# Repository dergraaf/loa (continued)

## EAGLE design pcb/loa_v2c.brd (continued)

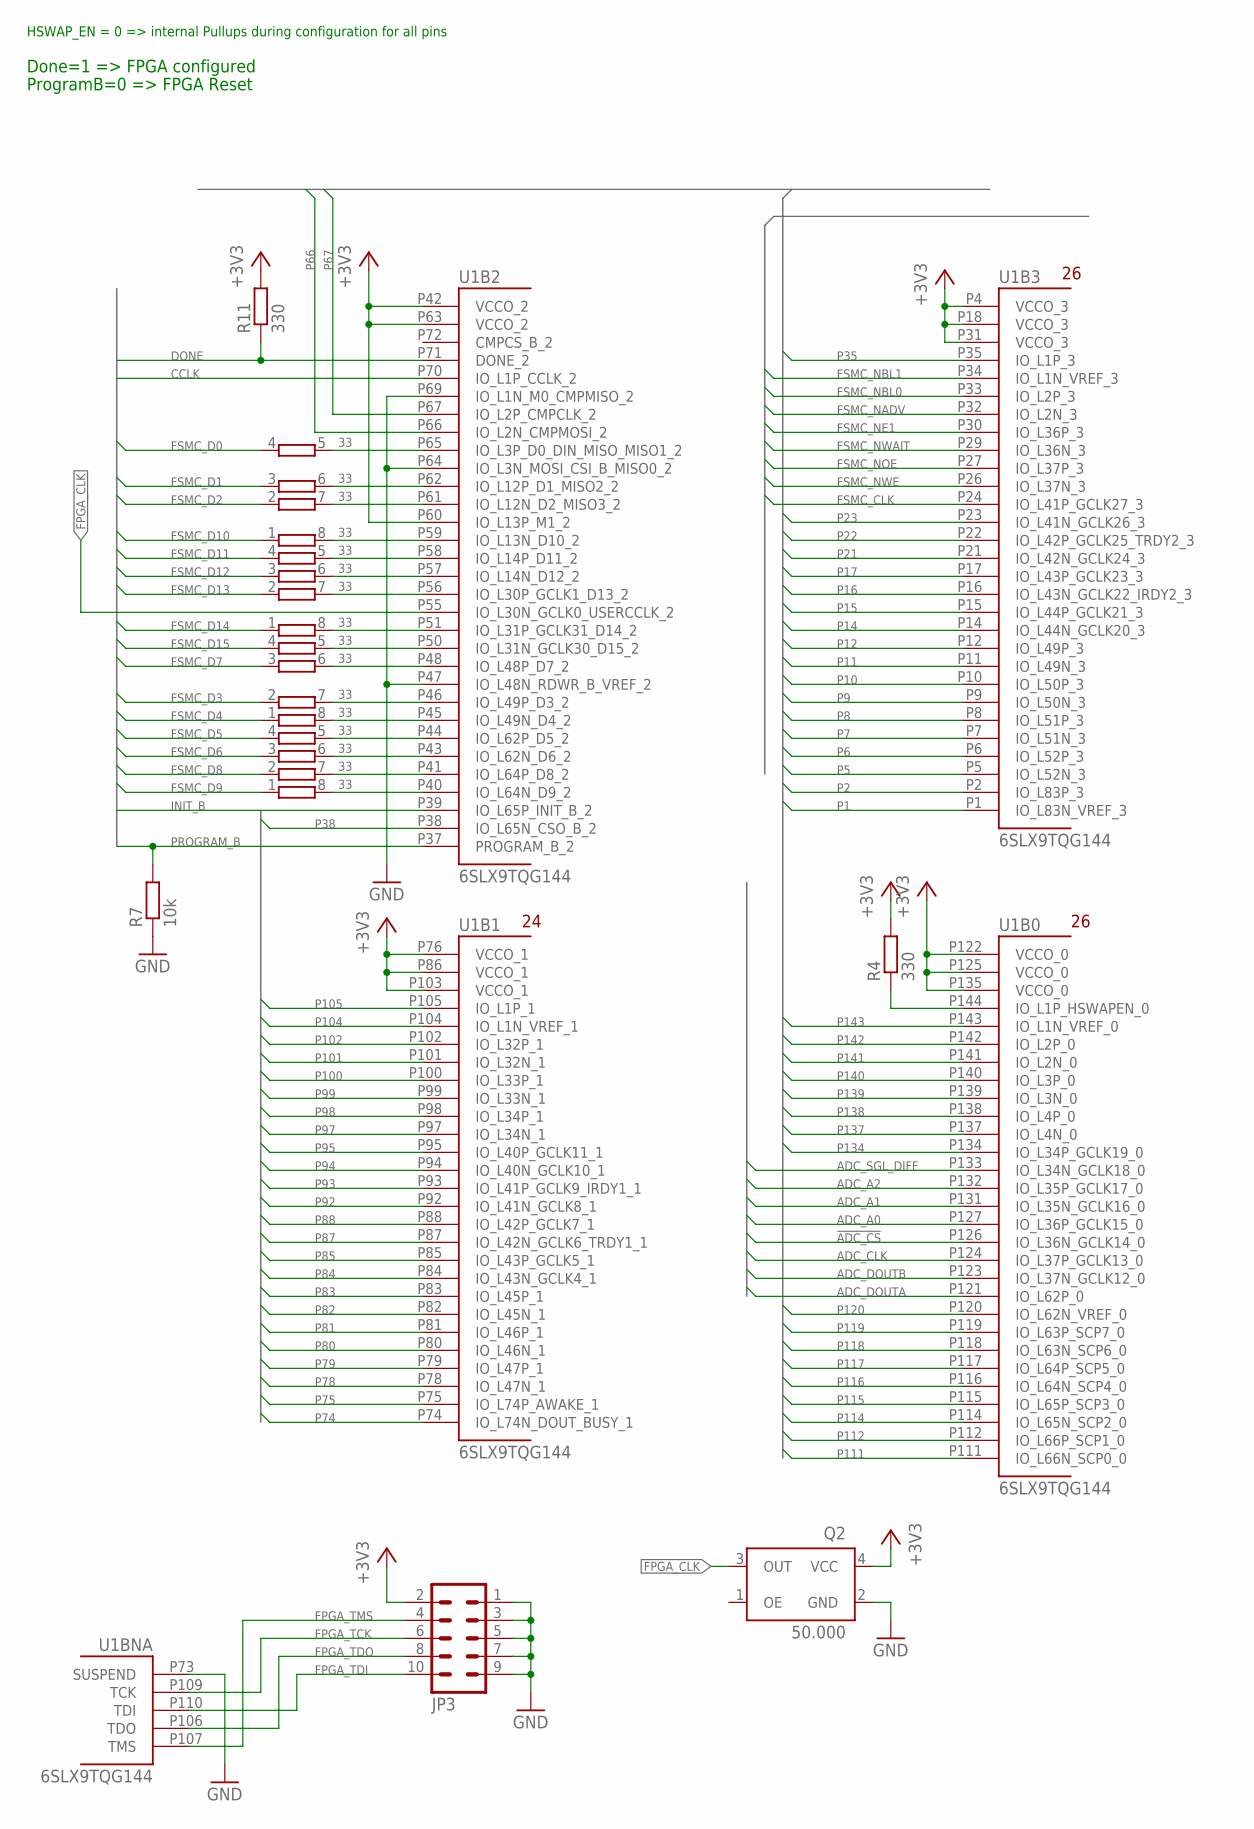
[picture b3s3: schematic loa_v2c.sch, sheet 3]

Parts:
JP3: ML10S
Q2: 50.000; XO53
R4, R11: 330; R0603
R7: 10k; R0603
RN3, RN4, RN6, RN7: 33; EXB38V
U1: 6SLX9TQG144; TQ144

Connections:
!ADC_CS: U1.P126 (IO_L36N_GCLK14_0); also elsewhere on the board
+3V3: JP3.2, Q2.4 (VCC), R4.2, R11.2, U1.P4 (VCCO_3), U1.P18 (VCCO_3), U1.P31 (VCCO_3), U1.P42 (VCCO_2), U1.P60 (IO_L13P_M1_2), U1.P63 (VCCO_2), U1.P76 (VCCO_1), U1.P86 (VCCO_1), U1.P103 (VCCO_1), U1.P122 (VCCO_0), U1.P125 (VCCO_0), U1.P135 (VCCO_0); also elsewhere on the board
ADC_A0: U1.P127 (IO_L36P_GCLK15_0); also elsewhere on the board
ADC_A1: U1.P131 (IO_L35N_GCLK16_0); also elsewhere on the board
ADC_A2: U1.P132 (IO_L35P_GCLK17_0); also elsewhere on the board
ADC_CLK: U1.P124 (IO_L37P_GCLK13_0); also elsewhere on the board
ADC_DOUTA: U1.P121 (IO_L62P_0); also elsewhere on the board
ADC_DOUTB: U1.P123 (IO_L37N_GCLK12_0); also elsewhere on the board
ADC_SGL_DIFF: U1.P133 (IO_L34N_GCLK18_0); also elsewhere on the board
CCLK: U1.P70 (IO_L1P_CCLK_2); also elsewhere on the board
DONE: R11.1, U1.P71 (DONE_2); also elsewhere on the board
FPGA_CLK: Q2.3 (OUT), U1.P55 (IO_L30N_GCLK0_USERCCLK_2)
FPGA_TCK: JP3.6, U1.P109 (TCK)
FPGA_TDI: JP3.10, U1.P110 (TDI)
FPGA_TDO: JP3.8, U1.P106 (TDO)
FPGA_TMS: JP3.4, U1.P107 (TMS)
FSMC_CLK: U1.P24 (IO_L41P_GCLK27_3); also elsewhere on the board
FSMC_D0: RN3.4 (1); also elsewhere on the board
FSMC_D1: RN3.3 (1); also elsewhere on the board
FSMC_D2: RN3.2 (1); also elsewhere on the board
FSMC_D3: RN7.2 (1); also elsewhere on the board
FSMC_D4: RN7.1; also elsewhere on the board
FSMC_D5: RN4.4 (1); also elsewhere on the board
FSMC_D6: RN4.3 (1); also elsewhere on the board
FSMC_D7: RN7.3 (1); also elsewhere on the board
FSMC_D8: RN4.2 (1); also elsewhere on the board
FSMC_D9: RN4.1; also elsewhere on the board
FSMC_D10: RN3.1; also elsewhere on the board
FSMC_D11: RN6.4 (1); also elsewhere on the board
FSMC_D12: RN6.3 (1); also elsewhere on the board
FSMC_D13: RN6.2 (1); also elsewhere on the board
FSMC_D14: RN6.1; also elsewhere on the board
FSMC_D15: RN7.4 (1); also elsewhere on the board
FSMC_NADV: U1.P32 (IO_L2N_3); also elsewhere on the board
FSMC_NBL0: U1.P33 (IO_L2P_3); also elsewhere on the board
FSMC_NBL1: U1.P34 (IO_L1N_VREF_3); also elsewhere on the board
FSMC_NE1: U1.P30 (IO_L36P_3); also elsewhere on the board
FSMC_NOE: U1.P27 (IO_L37P_3); also elsewhere on the board
FSMC_NWAIT: U1.P29 (IO_L36N_3); also elsewhere on the board
FSMC_NWE: U1.P26 (IO_L37N_3); also elsewhere on the board
GND: JP3.1, JP3.3, JP3.5, JP3.7, JP3.9, Q2.2 (GND), R7.1, U1.P47 (IO_L48N_RDWR_B_VREF_2), U1.P64 (IO_L3N_MOSI_CSI_B_MISO0_2), U1.P69 (IO_L1N_M0_CMPMISO_2), U1.P73 (SUSPEND); also elsewhere on the board
INIT_B: U1.P39 (IO_L65P_INIT_B_2); also elsewhere on the board
unnamed: RN3.5 (2), U1.P65 (IO_L3P_D0_DIN_MISO_MISO1_2)
unnamed: RN3.6 (2), U1.P62 (IO_L12P_D1_MISO2_2)
unnamed: RN3.7 (2), U1.P61 (IO_L12N_D2_MISO3_2)
unnamed: RN3.8 (2), U1.P59 (IO_L13N_D10_2)
unnamed: RN6.5 (2), U1.P58 (IO_L14P_D11_2)
unnamed: RN6.6 (2), U1.P57 (IO_L14N_D12_2)
unnamed: RN6.7 (2), U1.P56 (IO_L30P_GCLK1_D13_2)
unnamed: RN6.8 (2), U1.P51 (IO_L31P_GCLK31_D14_2)
unnamed: RN7.5 (2), U1.P50 (IO_L31N_GCLK30_D15_2)
unnamed: RN7.6 (2), U1.P48 (IO_L48P_D7_2)
unnamed: RN7.7 (2), U1.P46 (IO_L49P_D3_2)
unnamed: RN7.8 (2), U1.P45 (IO_L49N_D4_2)
unnamed: RN4.5 (2), U1.P44 (IO_L62P_D5_2)
unnamed: R4.1, U1.P144 (IO_L1P_HSWAPEN_0)
unnamed: RN4.7 (2), U1.P41 (IO_L64P_D8_2)
unnamed: RN4.6 (2), U1.P43 (IO_L62N_D6_2)
unnamed: RN4.8 (2), U1.P40 (IO_L64N_D9_2)
P1: U1.P1 (IO_L83N_VREF_3); also elsewhere on the board
P2: U1.P2 (IO_L83P_3); also elsewhere on the board
P5: U1.P5 (IO_L52N_3); also elsewhere on the board
P6: U1.P6 (IO_L52P_3); also elsewhere on the board
P7: U1.P7 (IO_L51N_3); also elsewhere on the board
P8: U1.P8 (IO_L51P_3); also elsewhere on the board
P9: U1.P9 (IO_L50N_3); also elsewhere on the board
P10: U1.P10 (IO_L50P_3); also elsewhere on the board
P11: U1.P11 (IO_L49N_3); also elsewhere on the board
P12: U1.P12 (IO_L49P_3); also elsewhere on the board
P14: U1.P14 (IO_L44N_GCLK20_3); also elsewhere on the board
P15: U1.P15 (IO_L44P_GCLK21_3); also elsewhere on the board
P16: U1.P16 (IO_L43N_GCLK22_IRDY2_3); also elsewhere on the board
P17: U1.P17 (IO_L43P_GCLK23_3); also elsewhere on the board
P21: U1.P21 (IO_L42N_GCLK24_3); also elsewhere on the board
P22: U1.P22 (IO_L42P_GCLK25_TRDY2_3); also elsewhere on the board
P23: U1.P23 (IO_L41N_GCLK26_3); also elsewhere on the board
P35: U1.P35 (IO_L1P_3); also elsewhere on the board
P38: U1.P38 (IO_L65N_CSO_B_2); also elsewhere on the board
P66: U1.P66 (IO_L2N_CMPMOSI_2); also elsewhere on the board
P67: U1.P67 (IO_L2P_CMPCLK_2); also elsewhere on the board
P74: U1.P74 (IO_L74N_DOUT_BUSY_1); also elsewhere on the board
P75: U1.P75 (IO_L74P_AWAKE_1); also elsewhere on the board
P78: U1.P78 (IO_L47N_1); also elsewhere on the board
P79: U1.P79 (IO_L47P_1); also elsewhere on the board
P80: U1.P80 (IO_L46N_1); also elsewhere on the board
P81: U1.P81 (IO_L46P_1); also elsewhere on the board
P82: U1.P82 (IO_L45N_1); also elsewhere on the board
P83: U1.P83 (IO_L45P_1); also elsewhere on the board
P84: U1.P84 (IO_L43N_GCLK4_1); also elsewhere on the board
P85: U1.P85 (IO_L43P_GCLK5_1); also elsewhere on the board
P87: U1.P87 (IO_L42N_GCLK6_TRDY1_1); also elsewhere on the board
P88: U1.P88 (IO_L42P_GCLK7_1); also elsewhere on the board
P92: U1.P92 (IO_L41N_GCLK8_1); also elsewhere on the board
P93: U1.P93 (IO_L41P_GCLK9_IRDY1_1); also elsewhere on the board
P94: U1.P94 (IO_L40N_GCLK10_1); also elsewhere on the board
P95: U1.P95 (IO_L40P_GCLK11_1); also elsewhere on the board
P97: U1.P97 (IO_L34N_1); also elsewhere on the board
P98: U1.P98 (IO_L34P_1); also elsewhere on the board
P99: U1.P99 (IO_L33N_1); also elsewhere on the board
P100: U1.P100 (IO_L33P_1); also elsewhere on the board
P101: U1.P101 (IO_L32N_1); also elsewhere on the board
P102: U1.P102 (IO_L32P_1); also elsewhere on the board
P104: U1.P104 (IO_L1N_VREF_1); also elsewhere on the board
P105: U1.P105 (IO_L1P_1); also elsewhere on the board
P111: U1.P111 (IO_L66N_SCP0_0); also elsewhere on the board
P112: U1.P112 (IO_L66P_SCP1_0); also elsewhere on the board
P114: U1.P114 (IO_L65N_SCP2_0); also elsewhere on the board
P115: U1.P115 (IO_L65P_SCP3_0); also elsewhere on the board
P116: U1.P116 (IO_L64N_SCP4_0); also elsewhere on the board
P117: U1.P117 (IO_L64P_SCP5_0); also elsewhere on the board
P118: U1.P118 (IO_L63N_SCP6_0); also elsewhere on the board
P119: U1.P119 (IO_L63P_SCP7_0); also elsewhere on the board
P120: U1.P120 (IO_L62N_VREF_0); also elsewhere on the board
P134: U1.P134 (IO_L34P_GCLK19_0); also elsewhere on the board
P137: U1.P137 (IO_L4N_0); also elsewhere on the board
P138: U1.P138 (IO_L4P_0); also elsewhere on the board
P139: U1.P139 (IO_L3N_0); also elsewhere on the board
P140: U1.P140 (IO_L3P_0); also elsewhere on the board
P141: U1.P141 (IO_L2N_0); also elsewhere on the board
P142: U1.P142 (IO_L2P_0); also elsewhere on the board
P143: U1.P143 (IO_L1N_VREF_0); also elsewhere on the board
PROGRAM_B: R7.2, U1.P37 (PROGRAM_B_2); also elsewhere on the board

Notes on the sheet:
Done=1 => FPGA configured
ProgramB=0 => FPGA Reset
HSWAP_EN = 0 => internal Pullups during configuration for all pins

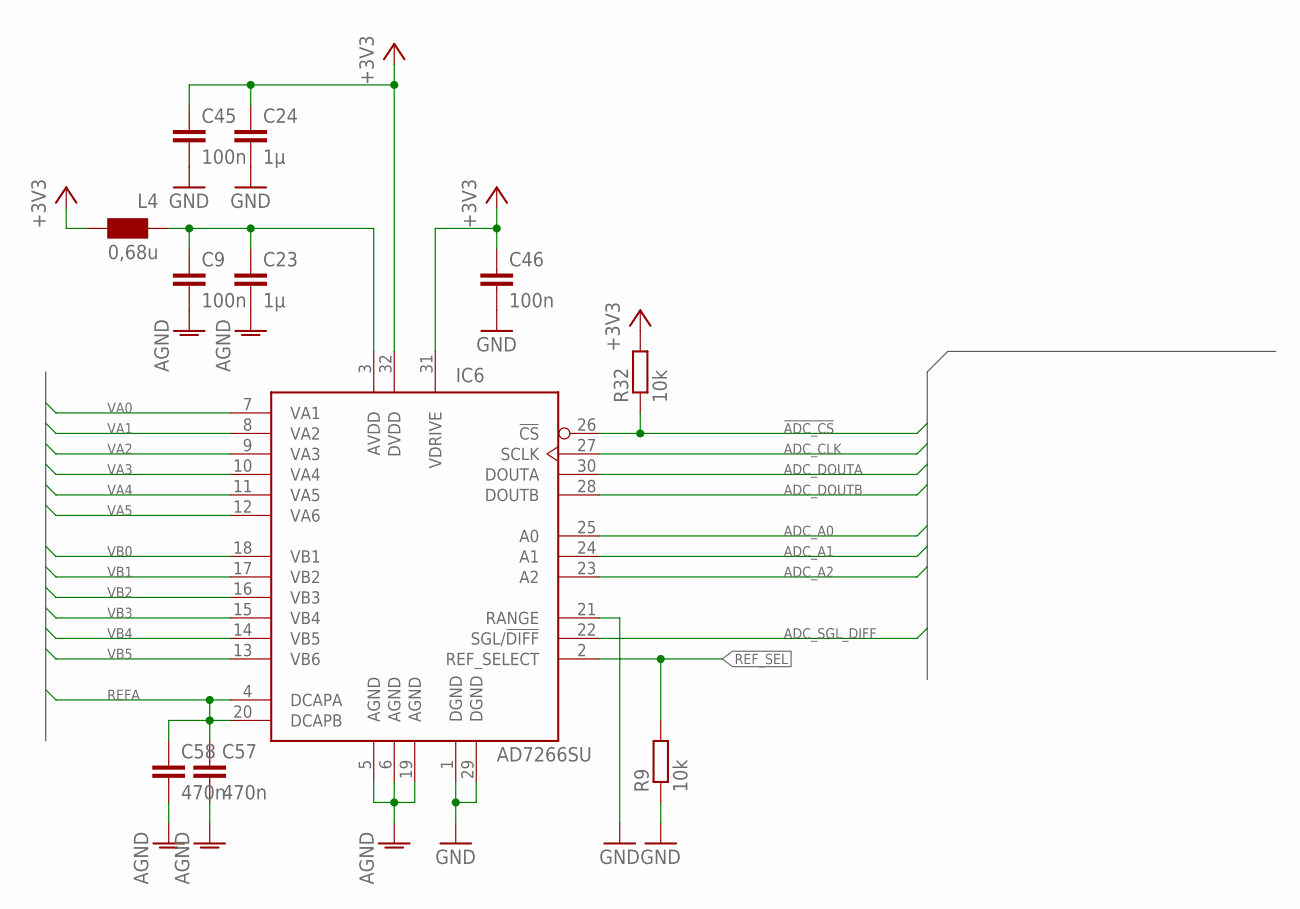
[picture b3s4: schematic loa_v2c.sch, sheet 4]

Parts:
C9, C45, C46: 100n; C0603
C23, C24: 1µ; C0805
C57, C58: 470n; C0805
IC6: AD7266SU; TQFP32-08
L4: 0,68u; WE-KI_0805_B
R9, R32: 10k; R0603

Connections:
!ADC_CS: IC6.26 (!CS), R32.1; also elsewhere on the board
+3V3: C24.1, C45.1, C46.1, IC6.31 (VDRIVE), IC6.32 (DVDD), L4.1 (2), R32.2; also elsewhere on the board
ADC_A0: IC6.25 (A0); also elsewhere on the board
ADC_A1: IC6.24 (A1); also elsewhere on the board
ADC_A2: IC6.23 (A2); also elsewhere on the board
ADC_CLK: IC6.27 (SCLK); also elsewhere on the board
ADC_DOUTA: IC6.30 (DOUTA); also elsewhere on the board
ADC_DOUTB: IC6.28 (DOUTB); also elsewhere on the board
ADC_SGL_DIFF: IC6.22 (SGL/!DIFF); also elsewhere on the board
AGND: C9.2, C23.2, C57.2, C58.2, IC6.5 (AGND), IC6.6 (AGND), IC6.19 (AGND); also elsewhere on the board
GND: C24.2, C45.2, C46.2, IC6.1 (DGND), IC6.21 (RANGE), IC6.29 (DGND), R9.1; also elsewhere on the board
unnamed: C9.1, C23.1, IC6.3 (AVDD), L4.2 (1)
REFA: C57.1, C58.1, IC6.4 (DCAPA), IC6.20 (DCAPB); also elsewhere on the board
REF_SEL: IC6.2 (REF_SELECT), R9.2; also elsewhere on the board
VA0: IC6.7 (VA1); also elsewhere on the board
VA1: IC6.8 (VA2); also elsewhere on the board
VA2: IC6.9 (VA3); also elsewhere on the board
VA3: IC6.10 (VA4); also elsewhere on the board
VA4: IC6.11 (VA5); also elsewhere on the board
VA5: IC6.12 (VA6); also elsewhere on the board
VB0: IC6.18 (VB1); also elsewhere on the board
VB1: IC6.17 (VB2); also elsewhere on the board
VB2: IC6.16 (VB3); also elsewhere on the board
VB3: IC6.15 (VB4); also elsewhere on the board
VB4: IC6.14 (VB5); also elsewhere on the board
VB5: IC6.13 (VB6); also elsewhere on the board

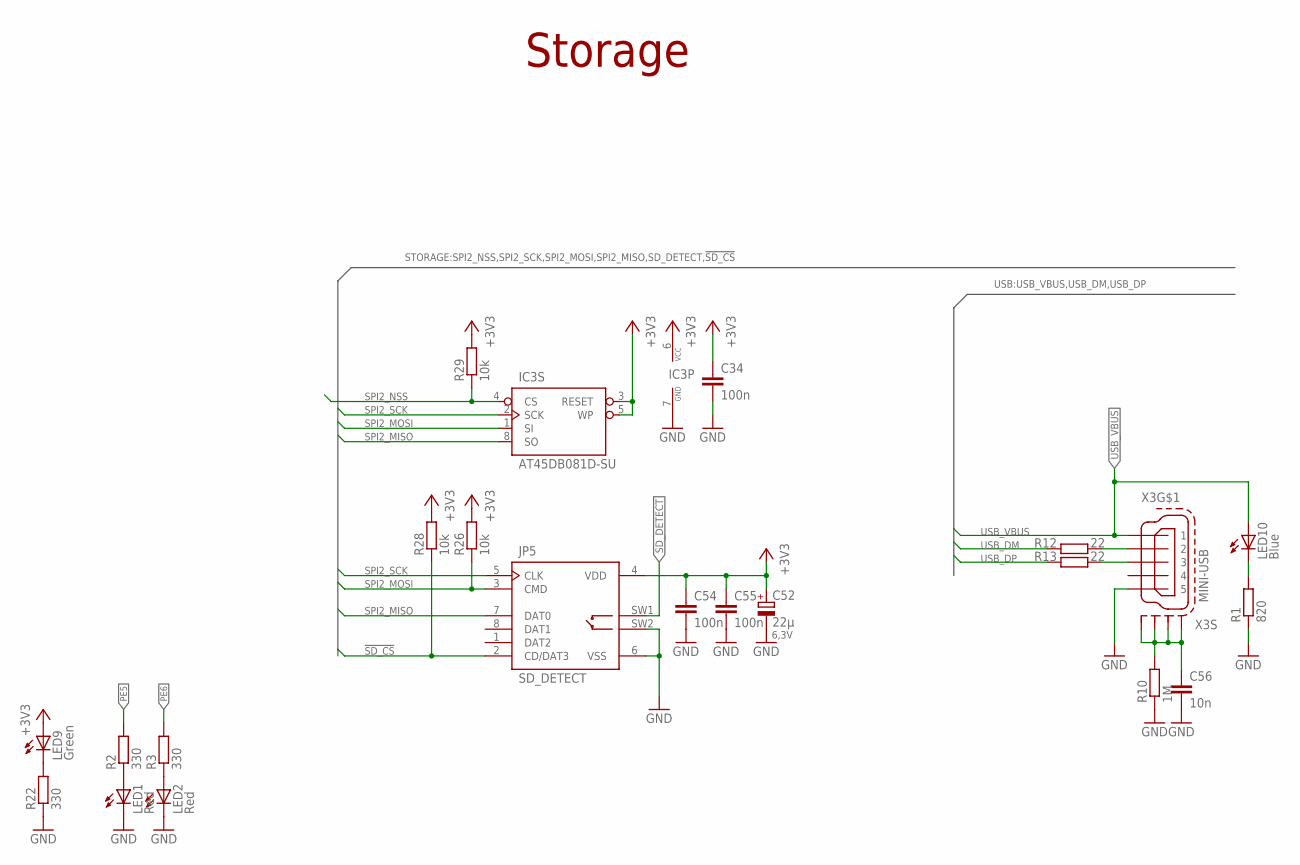
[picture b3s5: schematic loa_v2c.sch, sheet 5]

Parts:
C34, C54, C55: 100n; C0603
C52: 22µ; SMC_C; VOLTAGE 6,3V
C56: 10n; C0603
IC3: AT45DB081D-SU; SO08
JP5: SD_DETECT; SD_MOLEX_49225-0821
LED1, LED2: Red; CHIPLED_0805
LED9: Green; CHIPLED_0805
LED10: Blue; CHIPLED_0805
R1: 820; R0805
R2, R3, R22: 330; R0603
R10: 1M; R0805
R12, R13: 22; R0603
R26, R28, R29: 10k; R0603
X3: MINI-USB; 32005-201

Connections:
!SD_CS: JP5.2 (CD/DAT3), R28.1; also elsewhere on the board
+3V3: C34.1, C52.+, C54.1, C55.1, IC3.3 (RESET), IC3.5 (WP), IC3.6 (VCC), JP5.4 (VDD), LED9.A, R26.2, R28.2, R29.2; also elsewhere on the board
GND: C34.2, C52.-, C54.2, C55.2, C56.2, IC3.7 (GND), JP5.6 (VSS), JP5.SW2, LED1.C, LED2.C, R1.1, R10.1, R22.1, X3.5; also elsewhere on the board
unnamed: LED1.A, R2.1
unnamed: R12.2, X3.2
unnamed: R13.2, X3.3
unnamed: LED2.A, R3.1
unnamed: LED9.C, R22.2
unnamed: LED10.C, R1.2
unnamed: C56.1, R10.2, X3.M1 (S1), X3.M2 (S2), X3.M3 (S3), X3.M4 (S4)
PE5: R2.2; also elsewhere on the board
PE6: R3.2; also elsewhere on the board
SD_DETECT: JP5.SW1; also elsewhere on the board
SPI2_MISO: IC3.8 (SO), JP5.7 (DAT0); also elsewhere on the board
SPI2_MOSI: IC3.1 (SI), JP5.3 (CMD), R26.1; also elsewhere on the board
SPI2_NSS: IC3.4 (CS), R29.1; also elsewhere on the board
SPI2_SCK: IC3.2 (SCK), JP5.5 (CLK); also elsewhere on the board
USB_DM: R12.1; also elsewhere on the board
USB_DP: R13.1; also elsewhere on the board
USB_VBUS: LED10.A, X3.1; also elsewhere on the board

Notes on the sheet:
Storage

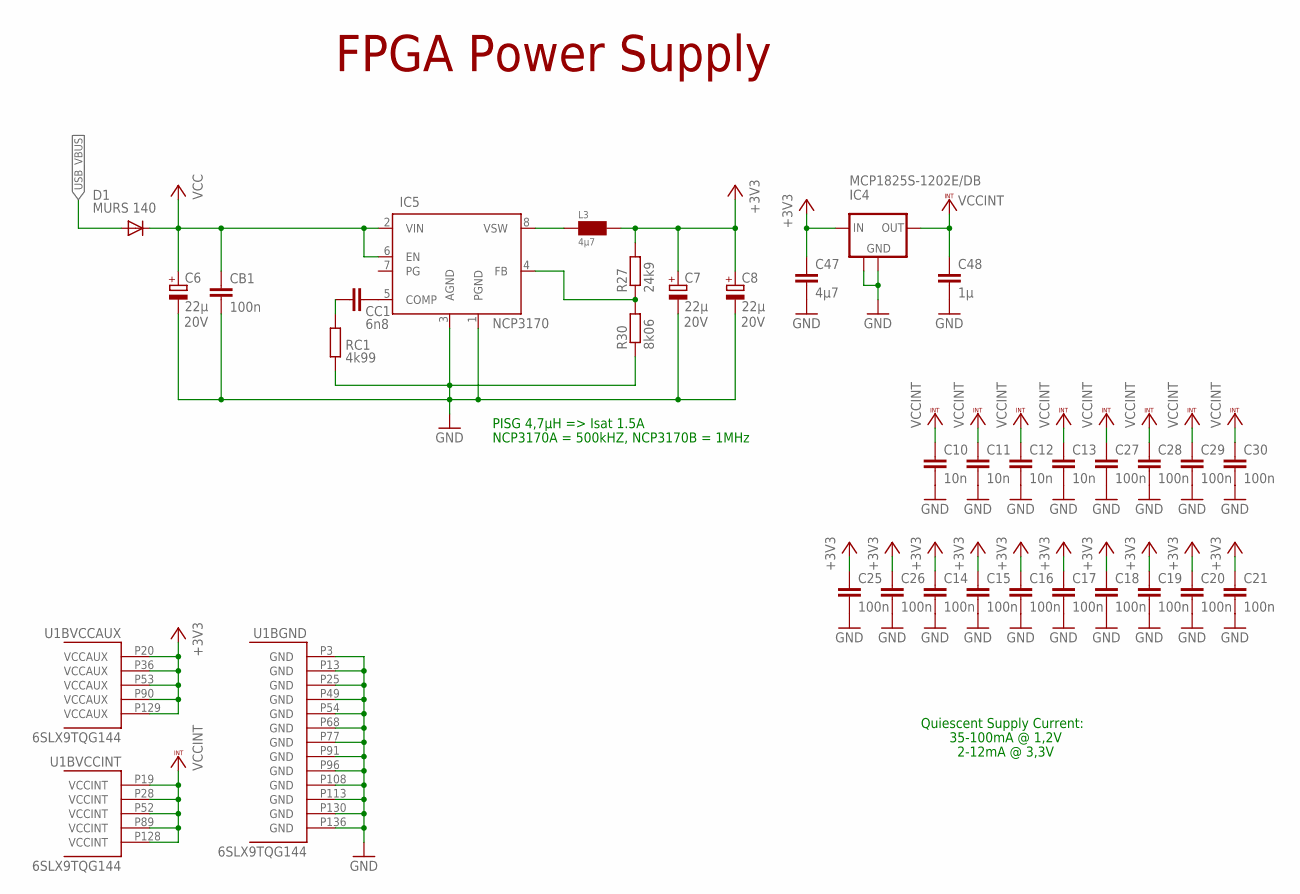
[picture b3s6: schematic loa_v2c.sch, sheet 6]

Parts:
C6: 22µ; SMC_D; VOLTAGE 20V
C7, C8: 22µ; SMC_C; VOLTAGE 20V
C10, C11, C12, C13: 10n; C0603
C14, C15, C16, C17, C18, C19, C20, C21, C25, C26, C27, C28, C29, C30: 100n; C0603
C47: 4µ7; C0805
C48: 1µ; C0805
CB1: 100n; C0603
CC1: 6n8; C0805
D1: MURS 140; SMB
IC4: MCP1825S-1202E/DB; SOT223
IC5: NCP3170; SO08
L3: 4µ7; L-PISG
R27: 24k9; M0805
R30: 8k06; M0805
RC1: 4k99; M0805
U1: 6SLX9TQG144; TQ144

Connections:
+3V3: C7.+, C8.+, C14.1, C15.1, C16.1, C17.1, C18.1, C19.1, C20.1, C21.1, C25.1, C26.1, C47.1, IC4.1 (IN), L3.2, R27.2, U1.P20 (VCCAUX), U1.P36 (VCCAUX), U1.P53 (VCCAUX), U1.P90 (VCCAUX), U1.P129 (VCCAUX); also elsewhere on the board
GND: C6.-, C7.-, C8.-, C10.2, C11.2, C12.2, C13.2, C14.2, C15.2, C16.2, C17.2, C18.2, C19.2, C20.2, C21.2, C25.2, C26.2, C27.2, C28.2, C29.2, C30.2, C47.2, C48.2, CB1.2, IC4.2 (GND), IC4.4 (GND), IC5.1 (PGND), IC5.3 (AGND), R30.1, RC1.1, U1.P3 (GND), U1.P13 (GND), U1.P25 (GND), U1.P49 (GND), U1.P54 (GND), U1.P68 (GND), U1.P77 (GND), U1.P91 (GND), U1.P96 (GND), U1.P108 (GND), U1.P113 (GND), U1.P130 (GND), U1.P136 (GND); also elsewhere on the board
unnamed: CC1.2, RC1.2
unnamed: CC1.1, IC5.5 (COMP)
unnamed: IC5.8 (VSW), L3.1
unnamed: IC5.4 (FB), R27.1, R30.2
USB_VBUS: D1.A; also elsewhere on the board
VCC: C6.+, CB1.1, D1.C, IC5.2 (VIN), IC5.6 (EN); also elsewhere on the board
VCCINT: C10.1, C11.1, C12.1, C13.1, C27.1, C28.1, C29.1, C30.1, C48.1, IC4.3 (OUT), U1.P19 (VCCINT), U1.P28 (VCCINT), U1.P52 (VCCINT), U1.P89 (VCCINT), U1.P128 (VCCINT)

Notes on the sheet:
35-100mA @ 1,2V
Quiescent Supply Current:
2-12mA @ 3,3V
FPGA Power Supply
PISG 4,7µH => Isat 1.5A
NCP3170A = 500kHZ, NCP3170B = 1MHz

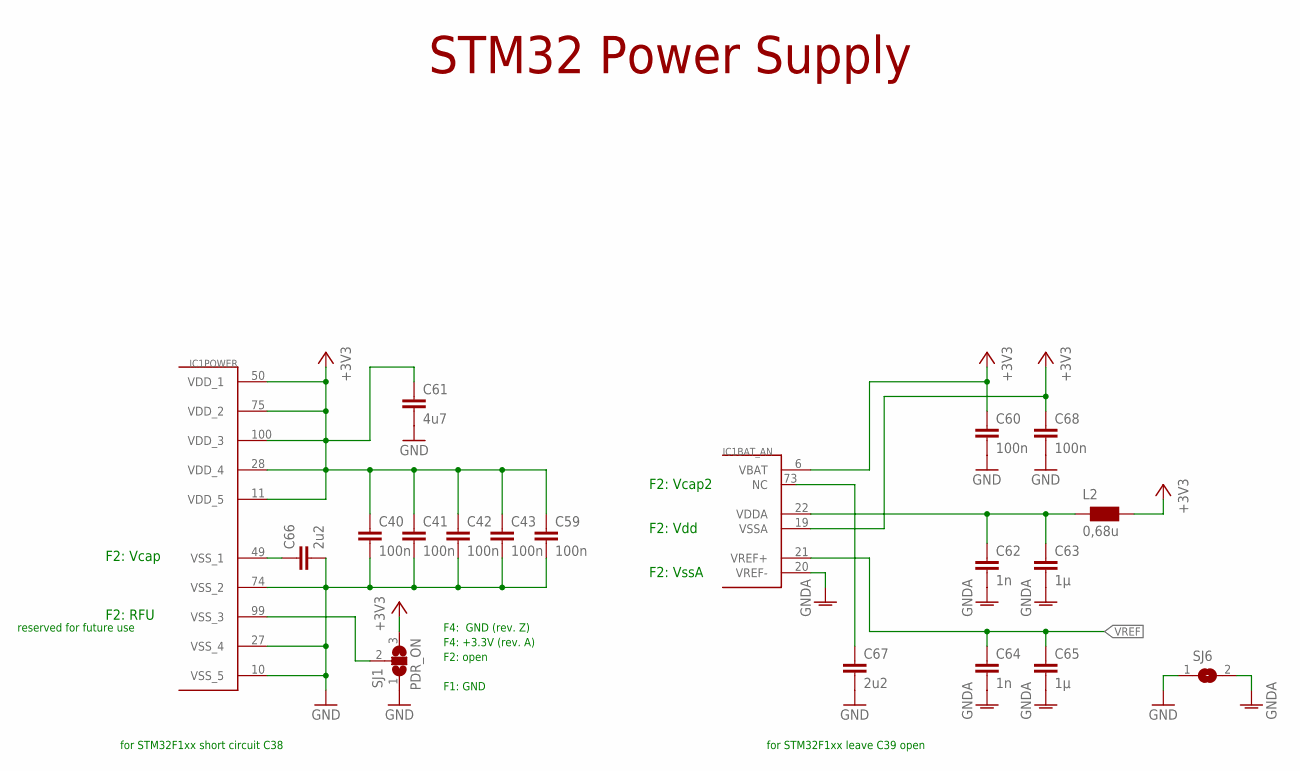
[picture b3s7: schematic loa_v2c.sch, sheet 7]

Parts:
C40, C41, C42, C43, C59, C60, C68: 100n; C0603
C61: 4u7; C0805
C62, C64: 1n; C0603
C63, C65: 1µ; C0805
C66, C67: 2u2; C0805
IC1: STM32F10XVXT6; TQFP100
L2: 0,68u; WE-KI_0805_B
SJ1: PDR_ON; SJ_2S
SJ6: SJS

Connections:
+3V3: C40.1, C41.1, C42.1, C43.1, C59.1, C60.1, C61.1, C68.1, IC1.6 (VBAT), IC1.11 (VDD_5), IC1.19 (VSSA), IC1.28 (VDD_4), IC1.50 (VDD_1), IC1.75 (VDD_2), IC1.100 (VDD_3), L2.1 (2), SJ1.3; also elsewhere on the board
GND: C40.2, C41.2, C42.2, C43.2, C59.2, C60.2, C61.2, C66.2, C67.2, C68.2, IC1.10 (VSS_5), IC1.27 (VSS_4), IC1.74 (VSS_2), SJ1.1, SJ6.1; also elsewhere on the board
GNDA: C62.2, C63.2, C64.2, C65.2, IC1.20 (VREF-), SJ6.2; also elsewhere on the board
unnamed: IC1.99 (VSS_3), SJ1.2
unnamed: C62.1, C63.1, IC1.22 (VDDA), L2.2 (1)
unnamed: C66.1, IC1.49 (VSS_1)
unnamed: C67.1, IC1.73 (NC)
VREF: C64.1, C65.1, IC1.21 (VREF+); also elsewhere on the board

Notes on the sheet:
F2: Vcap
F2: RFU
F2: Vdd
F2: VssA
F2: Vcap2
STM32 Power Supply
for STM32F1xx short circuit C38
reserved for future use
for STM32F1xx leave C39 open
F1: GND
F2: open
F4: +3.3V (rev. A)
F4: GND (rev. Z)

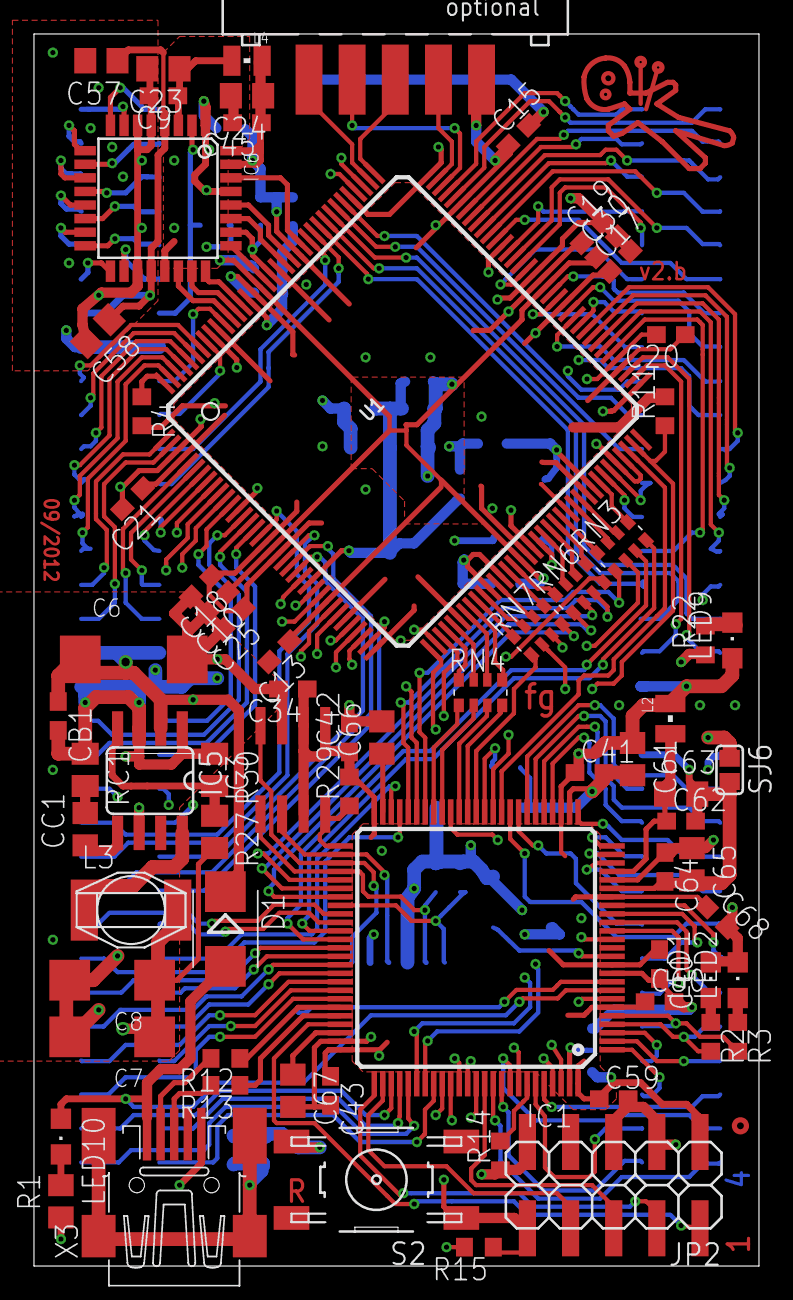
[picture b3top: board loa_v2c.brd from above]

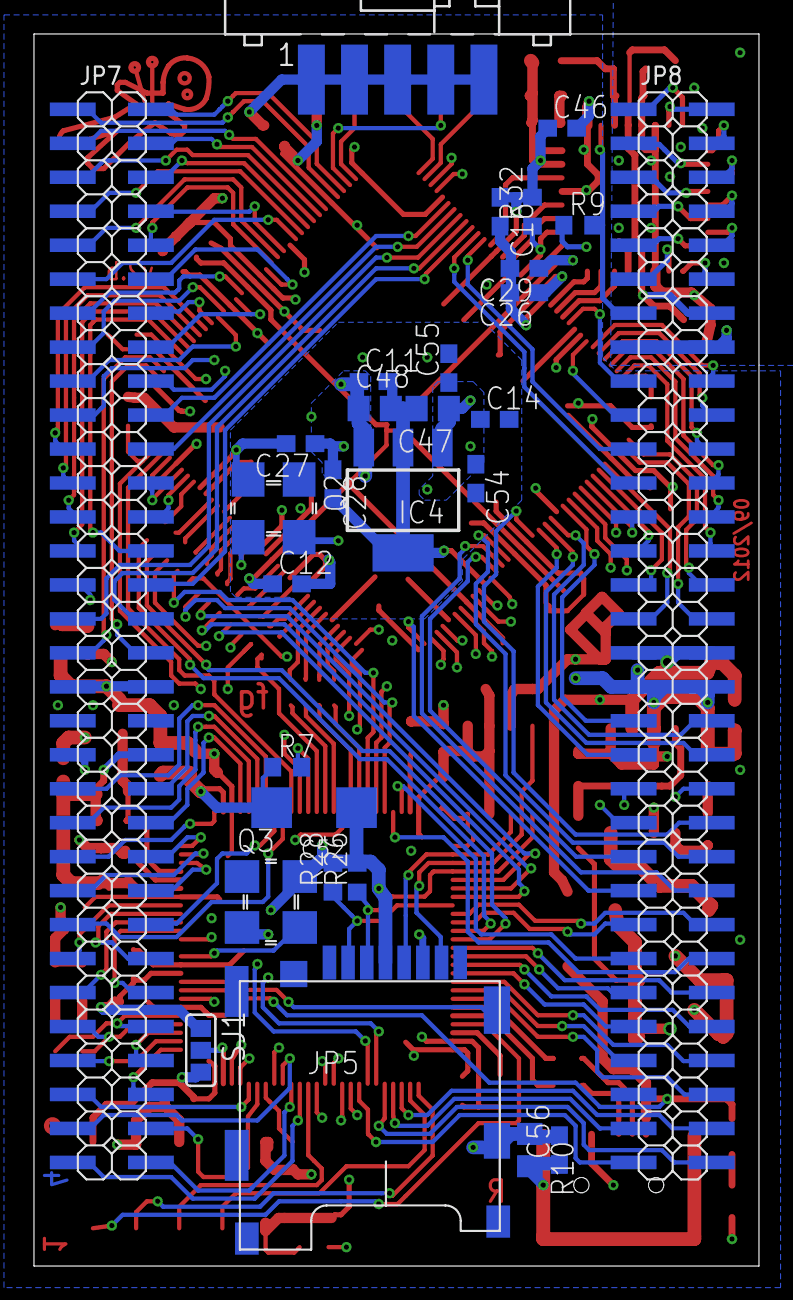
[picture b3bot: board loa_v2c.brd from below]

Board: 4 copper layers, 42.7 x 72.5 mm, 100 parts (29 on the bottom side), 212 nets.

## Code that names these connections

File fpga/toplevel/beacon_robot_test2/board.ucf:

# all IO-Pins are 3,3V
NET "*"			IOSTANDARD = LVCMOS33;

# ----------------------------------------------------------------------------
# Connections to the STM32F407
NET "cs_np"		LOC = P65;	# <- PA4
NET "sck_p"		LOC = P64;	# <- PA5
NET "miso_p"		LOC = P62;	# -> PA6
NET "mosi_p"		LOC = P61;	# <- PA7

# two-way handshake between FPGA and STM when new IR and US data is available
NET "ir_irq_p"	LOC = P60;	     	 # -> PE11
NET "ir_ack_p"	LOC = P51 | PULLDOWN;	 # <- PB10

NET "us_irq_p"	LOC = P57;		 # -- PE13
NET "us_ack_p" 	LOC = P59 | PULLDOWN;	 # -- PE12


# P44		# -- unconnected FPGA pin

# P48		# Init B -> PB11 (pullup needed)
# P51		# Din    <- PB10
# P53		# CCLK   <- PE15
# Prog B	(dedicated for configuration) <- PE10
# Done   	(dedicated for configuration) -> PE14

# User I/O after configuration:
# DIN, CCLK, DOUT

# ----------------------------------------------------------------------------
# 4 MBit SRAM CY7C1049DV33-10ZSXI (428-1982-ND)
NET "sram_addr_p<0>"	LOC = P56;
NET "sram_addr_p<1>"	LOC = P52;
NET "sram_addr_p<2>"	LOC = P50;
NET "sram_addr_p<3>"	LOC = P49;
NET "sram_addr_p<4>"	LOC = P46;
NET "sram_addr_p<5>"	LOC = P34;
NET "sram_addr_p<6>"	LOC = P33;
NET "sram_addr_p<7>"	LOC = P32;
NET "sram_addr_p<8>"	LOC = P31;
NET "sram_addr_p<9>"	LOC = P30;
NET "sram_addr_p<10>"	LOC = P78;
NET "sram_addr_p<11>"	LOC = P10;
NET "sram_addr_p<12>"	LOC = P12;
NET "sram_addr_p<13>"	LOC = P13;
NET "sram_addr_p<14>"	LOC = P15;
NET "sram_addr_p<15>"	LOC = P25;
NET "sram_addr_p<16>"	LOC = P27;
NET "sram_addr_p<17>"	LOC = P28;
NET "sram_addr_p<18>"	LOC = P29;

NET "sram_data_p<0>"	LOC = P41;
NET "sram_data_p<1>"	LOC = P40;
NET "sram_data_p<2>"	LOC = P37;
NET "sram_data_p<3>"	LOC = P36;
NET "sram_data_p<4>"	LOC = P16;
NET "sram_data_p<5>"	LOC = P19;
NET "sram_data_p<6>"	LOC = P20;
NET "sram_data_p<7>"	LOC = P23;

NET "sram_oe_np"	LOC = P24;
NET "sram_we_np"	LOC = P35;
NET "sram_ce_np"	LOC = P43;

# ----------------------------------------------------------------------------
# US TX
NET "us_tx0_p_high"	LOC = P93;
NET "us_tx0_p_low"	LOC = P94;
NET "us_tx1_p_high"	LOC = P98;
NET "us_tx1_p_low"	LOC = P99;
NET "us_tx2_p_high"	LOC = P3;
NET "us_tx2_p_low"	LOC = P4;

# ----------------------------------------------------------------------------
# US RX: one LTC2351 ADC
NET "us_rx_spi_in_p_sdo"		LOC = P85 | PULLDOWN;
NET "us_rx_spi_out_p_sck"		LOC = P84 | SLOW | DRIVE = 2;
NET "us_rx_spi_out_p_conv"		LOC = P77 | SLOW | DRIVE = 2;

# ----------------------------------------------------------------------------
# IR TX
NET "ir_tx_p"			LOC = P5;

# ----------------------------------------------------------------------------
# IR RX ADCs: two LTC2351 ADCs with common SCK and CONV
NET "ir_rx0_spi_in_p_sdo"		LOC = P89 | PULLDOWN;
NET "ir_rx1_spi_in_p_sdo"		LOC = P90 | PULLDOWN;
NET "ir_rx_spi_out_p_sck"		LOC = P88 | SLOW | DRIVE = 2;
NET "ir_rx_spi_out_p_conv"		LOC = P86 | SLOW | DRIVE = 2;



# ----------------------------------------------------------------------------
# Clock (connected to a 50 MHz oscillator)
NET "clk"		LOC = P83;
NET "clk"		TNM_NET = clk;
TIMESPEC TS_clk = PERIOD "clk" 50 MHz HIGH 50%;

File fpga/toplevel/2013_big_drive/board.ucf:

# All hardware directly situated on the LOA v2b / v2c board

# all IO-Pins are 3.3V
NET "*"			IOSTANDARD = LVCMOS33;

# ----------------------------------------------------------------------------
# Connections to the STM32F407
#?NET "load_p"	LOC = P55;	# PE7
#?NET "reset_n"	LOC = P56;	# PB2 (BOOT0)

# ----------------------------------------------------------------------------
# Connections between stm and fpga

# Clock (connected to a 50 MHz oscillator)
NET "clk"		LOC = P55;
NET "clk"		TNM_NET = clk;
TIMESPEC TS_clk = PERIOD "clk" 50 MHz HIGH 50%;




# ADC (connected via SPI)
NET "ADC_OUT_P_CS_N" 		LOC = P126; # !ADC_CS
NET "ADC_OUT_P_SCK" 		LOC = P124;
NET "ADC_IN_P_D_A" 		LOC = P121;
NET "ADC_IN_P_D_B"		LOC = P123;
NET "ADC_OUT_P_A<0>" 		LOC = P127;
NET "ADC_OUT_P_A<1>" 		LOC = P131;
NET "ADC_OUT_P_A<2>" 		LOC = P132;
NET "ADC_OUT_P_SGL_DIFF"	LOC = P133;



#JTAG:
#SUSPEND	P73
#TCK 		P109
#TDI		P110
#TDO		P106
#TMS		P107


# FSMC
# NET "FSMC_INOUT_P_D<0>"		LOC = P65; # D14
# NET "FSMC_INOUT_P_D<1>"		LOC = P62; # D15
# NET "FSMC_INOUT_P_D<2>"		LOC = P61; # D0
# NET "FSMC_INOUT_P_D<3>"		LOC = P46; # D1
# NET "FSMC_INOUT_P_D<4>"		LOC = P45; # E7
# NET "FSMC_INOUT_P_D<5>"		LOC = P44; # E8
# NET "FSMC_INOUT_P_D<6>"		LOC = P43; # E9
# NET "FSMC_INOUT_P_D<7>"		LOC = P48; # E10
# NET "FSMC_INOUT_P_D<8>"		LOC = P41; # E11
# NET "FSMC_INOUT_P_D<9>"		LOC = P40; # E12
# NET "FSMC_INOUT_P_D<10>"	LOC = P59; # E13
# NET "FSMC_INOUT_P_D<11>"	LOC = P58; # E14
# NET "FSMC_INOUT_P_D<12>"	LOC = P57; # E15
# NET "FSMC_INOUT_P_D<13>"	LOC = P56; # D8
# NET "FSMC_INOUT_P_D<14>"	LOC = P51; # D9
# NET "FSMC_INOUT_P_D<15>"	LOC = P50; # D10

# NET "FSMC_OUT_P_NADV"		LOC = P32; # B7
# NET "FSMC_OUT_P_CLK"		LOC = P24; # D3
# NET "FSMC_OUT_P_NOE"		LOC = P27; # D4
# NET "FSMC_OUT_P_NWE"		LOC = P26; # D5
# NET "FSMC_IN_P_NWAIT"	LOC = P29; # D6
# NET "FSMC_OUT_P_NE1"		LOC = P30; # D7
# NET "FSMC_OUT_P_NBL<0>"		LOC = P33; # E0
# NET "FSMC_OUT_P_NBL<1>"		LOC = P34; # E1

NET "LOAD_P"				LOC = P62;

NET "MOSI_P"		LOC = P56;
NET "MISO_P"		LOC = P51;
NET "SCK_P"		LOC = P50;
NET "CS_NP"		LOC = P65;

# Programming pins, may be used after configuration
# NET "DONE"			LOC = P71; # C13
# NET "PROGRAM_B"		LOC = P37; # B2/Boot1
# NET "INIT_B"		LOC = P39; # B1
# NET "CCLK"			LOC = P70; # B0

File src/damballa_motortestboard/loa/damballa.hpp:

#ifndef LOA_HPP
#define LOA_HPP

#include <xpcc/architecture.hpp>
#include <xpcc/driver/connectivity/software_spi.hpp>
#include <xpcc/driver/storage/at45db0x1d.hpp>

namespace loa
{
	GPIO__OUTPUT(Led1, E, 3);
	GPIO__OUTPUT(Led2, E, 4);
	GPIO__OUTPUT(Led3, E, 5);
	GPIO__OUTPUT(Led4, E, 6);
	
	typedef xpcc::gpio::Nibble<Led1, Led2, Led3, Led4> Leds;
	
	GPIO__INPUT(Button1, C, 13);
	GPIO__INPUT(Button2, E, 15);
	
	GPIO__OUTPUT(CsFlash, D, 11);
	GPIO__OUTPUT(CsSdCard, D, 3);
	
	/**
	 * USART3 configured as SPI Master
	 * 
	 * TX (MOSI) => PD8
	 * RX (MISO) => PD9
	 * CK (SCLK) => PD10
	 */
	//typedef xpcc::stm32::UsartSpi3 SpiFlash;
	GPIO__OUTPUT(Mosi, D, 8);
	GPIO__INPUT(Miso, D, 9);
	GPIO__OUTPUT(Sck, D, 10);
	
	typedef xpcc::SoftwareSpi<Sck, Mosi, Miso, 40000000> SpiFlash;
	extern SpiFlash spiFlash;
	
	extern xpcc::At45db0x1d<SpiFlash, CsFlash> dataflash;
	
	extern xpcc::stm32::Can1 can;
	
	namespace fpga
	{
		/**
		 * Chip Select during normal operation, DIN during configuration
		 */
		GPIO__OUTPUT(Cs, A, 4);
		extern xpcc::stm32::Spi1 spi;
		
		/**
		 * Driven low during before configuration.
		 * 
		 * After it goes high the M[2:0] pins are sampled and the configuration
		 * is started. Holding the pin low stalls the configuration start.
		 * 
		 * During configuration the FPGA indicates the occurrence of a
		 * configuration data error (i.e., CRC error) by asserting INIT_B Low.
		 * After configuration successfully completes, i.e., when the DONE pin
		 * goes High, the INIT_B pin is available as a full user-I/O pin.
		 */
		GPIO__INPUT(InitB, A, 8);
		
		/**
		 * Load/Store 
		 * 
		 * A rising edge stores the encoder values etc.
		 */
		GPIO__OUTPUT(Load, E, 7);
		
		/**
		 * FPGA Reset
		 * 
		 * Low active. Can be used to reset the internal logic of the FPGA.
		 */
		GPIO__OUTPUT(Reset, B, 2);
		
		// TODO
		GPIO__IO(Unused, E, 2);
	}
	
	// ----------------------------------------------------------------------------
	/**
	 * Peripherals of the Damballa Board
	 * 
	 * 
	 */
	class Damballa
	{
	public:
		/**
		 * Initialize the predefined IO-Pins and load the FPGA configuration
		 */
		static bool
		initialize();
		
		/// Load values into the internal buffers (e.g. encoder values)
		static void
		load();
		
		static void
		writeWord(uint16_t address, uint16_t data);
		
		static uint16_t
		readWord(uint16_t address);
		
		/**
		 * Reloads the FPGA configuration from the dataflash into
		 * the FPGA.
		 * 
		 * \return 	\c true if the configuration was successful loaded.
		 */
		static bool
		reconfigureFpga();
		
	private:
		/// Configure the SPI interface to the FPGA
		static void
		configureSpiFpga();
		/**
		 * Load the configuration into the FPGA
		 */
		static bool
		configureFpga();
		
		/**
		 * Puts the pins used for configuration in an safe state to avoid
		 * drawing constant current over one of the pull-up resistors.
		 */
		static void
		deassertFpgaConfiguration();
	};
}

#endif // LOA_HPP

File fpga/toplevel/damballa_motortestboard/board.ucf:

# all IO-Pins are 3,3V
NET "*"			IOSTANDARD = LVCMOS33;

# ----------------------------------------------------------------------------
# Connections to the STM32F407
NET "cs_np"		LOC = P65;
NET "sck_p"		LOC = P53;
NET "miso_p"	LOC = P60;
NET "mosi_p"	LOC = P59;

NET "load_p"	LOC = P55;	# PE7
NET "reset_n"	LOC = P56;	# PB2 (BOOT0)

# P63 -> ? (PE2)
# P58 -> output, InitB	(PA8)

# ----------------------------------------------------------------------------
# Connections on the Damballa Board
NET "led_np<0>" LOC = P141;
NET "led_np<1>" LOC = P140;
NET "led_np<2>" LOC = P137;
NET "led_np<3>" LOC = P135;

NET "sw_np<0>"	LOC = P21;	# Button 3
NET "sw_np<1>"	LOC = P20;	# Button 4

# ADC (connected via SPI)
# ...

# Clock (connected to a 50 MHz oscillator)
NET "clk"		LOC = P127;
NET "clk"		TNM_NET = clk;
TIMESPEC TS_clk = PERIOD "clk" 50 MHz HIGH 50%;
